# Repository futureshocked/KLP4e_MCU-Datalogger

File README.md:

# MCU-Datalogger

This is the repository for the "MCU Datalogger" project.

This is one of the projects from the course [KiCad Like a Pro, 4th edition](https://techexplorations.com/so/kicad-like-a-pro-4th-edition).

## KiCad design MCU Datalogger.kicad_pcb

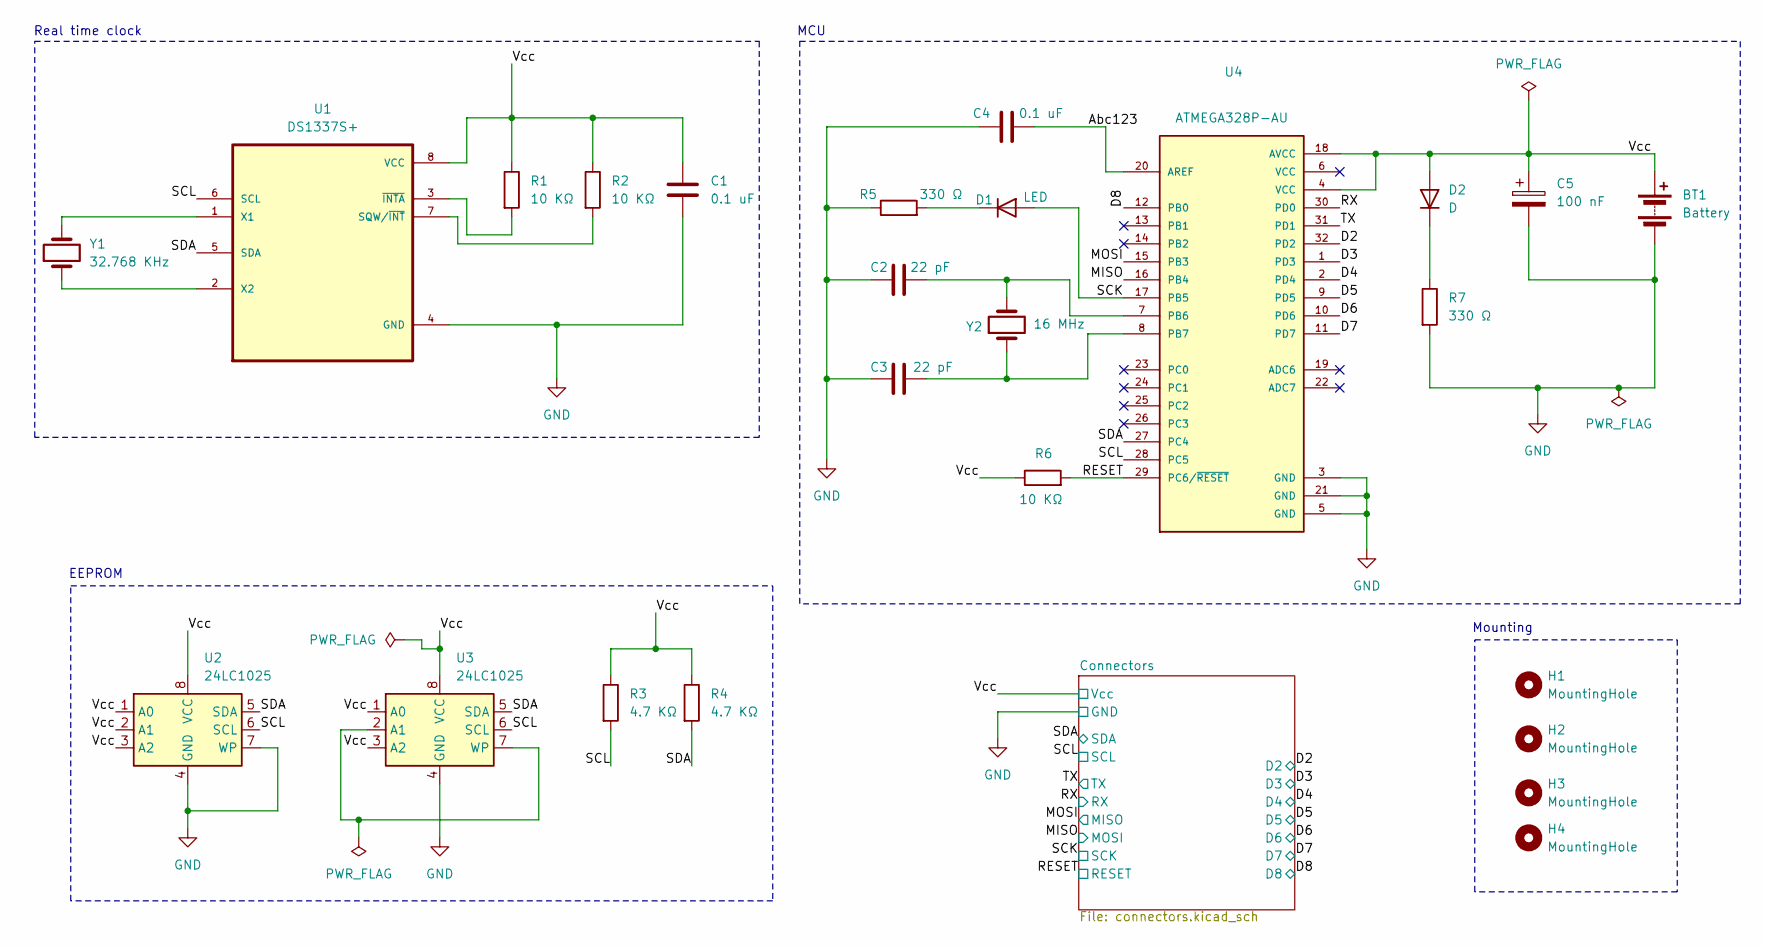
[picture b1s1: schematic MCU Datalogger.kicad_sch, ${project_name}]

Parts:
BT1: Battery; PinHeader_1x02_P2.54mm_Vertical
C1, C4: 0.1 uF; C_0805_2012Metric
C2, C3: 22 pF; C_0805_2012Metric
C5: 100 nF; C_0805_2012Metric
D1: LED; LED_0805_2012Metric
D2: D; LED_0805_2012Metric
H1, H2, H3, H4: MountingHole; MountingHole_2.1mm
R1, R2, R6: 10 ΚΩ; R_0805_2012Metric
R3, R4: 4.7 ΚΩ; R_0805_2012Metric
R5, R7: 330 Ω; R_0805_2012Metric
U1: DS1337S+; SOIC127P600X175-8N
U2, U3: 24LC1025; SOIC-8_5.23x5.23mm_P1.27mm
U4: ATMEGA328P-AU; QFP80P900X900X120-32N
Y1: 32.768 KHz; Crystal_SMD_5032-2Pin_5.0x3.2mm_HandSoldering
Y2: 16 MHz; Crystal_SMD_5032-2Pin_5.0x3.2mm_HandSoldering

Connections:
/Abc123: C4.2, U4.20 (AREF)
/D2: U4.32 (PD2); also elsewhere on the board
/D3: U4.1 (PD3); also elsewhere on the board
/D4: U4.2 (PD4); also elsewhere on the board
/D5: U4.9 (PD5); also elsewhere on the board
/D6: U4.10 (PD6); also elsewhere on the board
/D7: U4.11 (PD7); also elsewhere on the board
/D8: U4.12 (PB0); also elsewhere on the board
/MISO: U4.16 (PB4); also elsewhere on the board
/MOSI: U4.15 (PB3); also elsewhere on the board
/RESET: R6.2, U4.29 (PC6/~RESET); also elsewhere on the board
/RX: U4.30 (PD0); also elsewhere on the board
/SCK: D1.2 (A), U4.17 (PB5); also elsewhere on the board
/SCL: R3.2, U1.6 (SCL), U2.6 (SCL), U3.6 (SCL), U4.28 (PC5); also elsewhere on the board
/SDA: R4.2, U1.5 (SDA), U2.5 (SDA), U3.5 (SDA), U4.27 (PC4); also elsewhere on the board
/TX: U4.31 (PD1); also elsewhere on the board
/Vcc: BT1.1 (+), C1.1, C5.1, D2.2 (A), R1.1, R2.1, R3.1, R4.1, R6.1, U1.8 (VCC), U2.1 (A0), U2.2 (A1), U2.3 (A2), U2.8 (VCC), U3.1 (A0), U3.3 (A2), U3.8 (VCC), U4.4 (VCC), U4.18 (AVCC); also elsewhere on the board
GND: BT1.2 (-), C1.2, C2.2, C3.1, C4.1, C5.2, R5.1, R7.2, U1.4 (GND), U2.4 (GND), U2.7 (WP), U3.4 (GND), U4.3 (GND), U4.5 (GND), U4.21 (GND); also elsewhere on the board
unnamed: D1.1 (K), R5.2
unnamed: D2.1 (K), R7.1
unnamed: R2.2, U1.7 (SQW/~INT)
unnamed: U1.1 (X1), Y1.2
unnamed: U1.2 (X2), Y1.1
unnamed: R1.2, U1.3 (~INTA)
unnamed: U3.2 (A1), U3.7 (WP)
unnamed: C2.1, U4.7 (PB6), Y2.2
unnamed: C3.2, U4.8 (PB7), Y2.1

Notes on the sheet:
Real time clock
MCU
Mounting
EEPROM

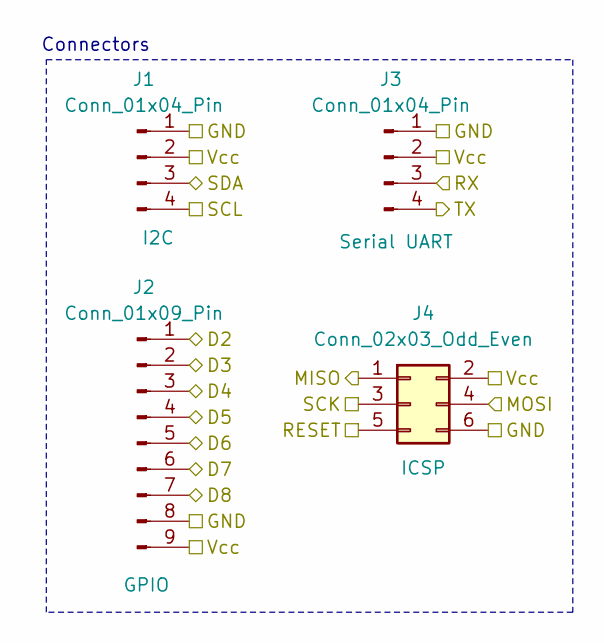
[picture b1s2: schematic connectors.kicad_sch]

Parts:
J1, J3: Conn_01x04_Pin; PinHeader_1x04_P2.54mm_Vertical
J2: Conn_01x09_Pin; PinHeader_1x09_P2.54mm_Vertical
J4: Conn_02x03_Odd_Even; PinHeader_2x03_P2.54mm_Vertical

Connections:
/D2: J2.1; also elsewhere on the board
/D3: J2.2; also elsewhere on the board
/D4: J2.3; also elsewhere on the board
/D5: J2.4; also elsewhere on the board
/D6: J2.5; also elsewhere on the board
/D7: J2.6; also elsewhere on the board
/D8: J2.7; also elsewhere on the board
/MISO: J4.4; also elsewhere on the board
/MOSI: J4.1; also elsewhere on the board
/RESET: J4.5; also elsewhere on the board
/RX: J3.3; also elsewhere on the board
/SCK: J4.3; also elsewhere on the board
/SCL: J1.4; also elsewhere on the board
/SDA: J1.3; also elsewhere on the board
/TX: J3.4; also elsewhere on the board
/Vcc: J1.2, J2.9, J3.2, J4.2; also elsewhere on the board
GND: J1.1, J2.8, J3.1, J4.6; also elsewhere on the board

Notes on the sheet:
Connectors

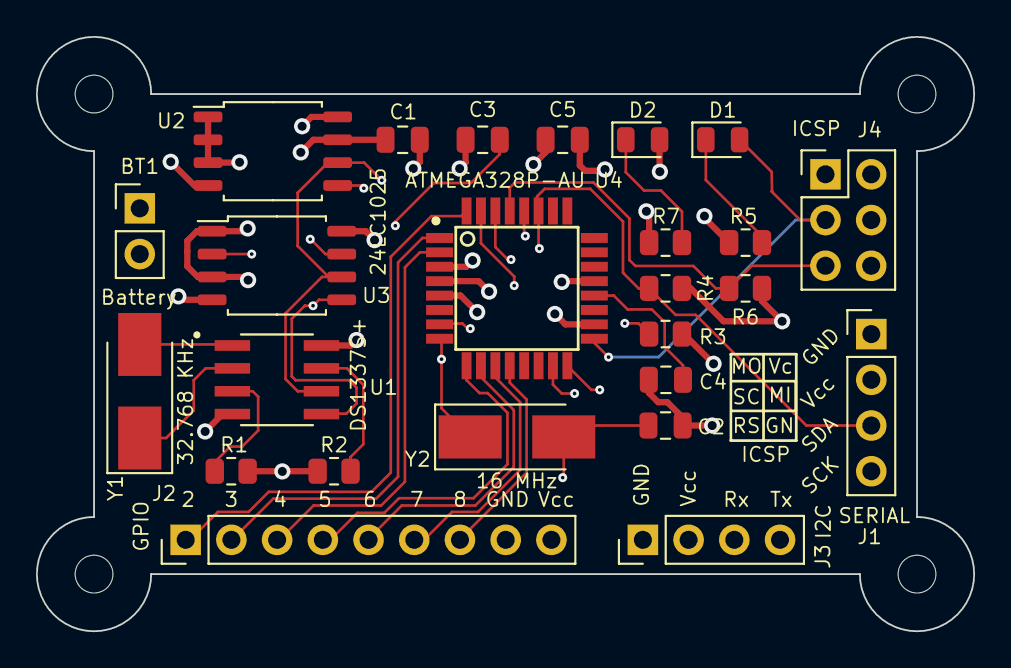
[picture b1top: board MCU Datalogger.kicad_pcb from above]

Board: 4 copper layers, 52.1 x 33.0 mm, 29 parts (0 on the bottom side), 27 nets.

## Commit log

2024-04-16 First commit of new project.
2024-04-16 Setup of the schematic editor for the new project.
2024-04-16 Updated gitignore file.
2024-04-17 Added required symbols to the schematic sheets.
2024-04-17 Changed locations of symbols (arrange).
2024-04-17 Added component values.
2024-04-17 Completed symbol—footprint associations.
2024-04-17 Completed wiring of main sheet.
2024-04-17 Allocated GND and Vcc nets to the Power net class.
2024-04-17 Using PWR_FLAG symbols to suppress to errors.
2024-04-17 Completed comments.
2024-04-17 Setup the PCB editor.
2024-04-17 Completed placement of footprints.
2024-04-17 Refined and completed outline
2024-04-17 Routing sans GND Vcc complete.
2024-04-17 Completed wiring. Many improvements pending.
2024-04-17 Fixed all issues and warnings, and refined routing.
2024-04-18 Ready to manufacture version 1.
2024-04-18 Completed 2-layer PCB project.
2024-04-18 Added missing 3D models.
2024-04-18 Added gerber directories and ZIP archives to .gitignore.
2024-04-18 Completed 4-layer pcb routing.
2024-04-18 Completed 4-layer PCB.
2024-04-18 Added gitattributes file to preven PCB Files from merging.
2024-04-18 Made small change to schematic.
2024-04-18 Minor changes.
2024-05-03 Small changes.
2025-03-11 Fixed error with the I2C clock signal.
2025-03-11 Fixed issue with I2C SCL.
2025-03-11 Fixed issue with I2C SCL signal.
